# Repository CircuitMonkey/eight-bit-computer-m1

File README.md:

# eight-bit-computer-m1
Surface Mount Technology (SMT) implementation of Ben Eater's 8-bit Computer

The "M1" project is a Surface Mount Technology (SMT) implementation of [Ben Eater's 8-bit computer project](https://eater.net/8bit) as a compact and modular kit designed in Autodesk Eagle.   If you don't want to mess with SMT or Eagle, Ben has made his kit PCB available in KiCAD already,  or consider purchasing his kit.

For this implementation, I have re-entered all of the design files and created new suirface-mount library components into Eagle, by hand.  Therefore there are likely to be a few errors or unexpected differences encountered. Your feedback would be much appreciated.

Circuit Monkey is not affiliated with Ben Eater. However, if you appreciate this or Ben's project, please consider supporting Ben's work directly and financially using any one of the methods listed on his website.

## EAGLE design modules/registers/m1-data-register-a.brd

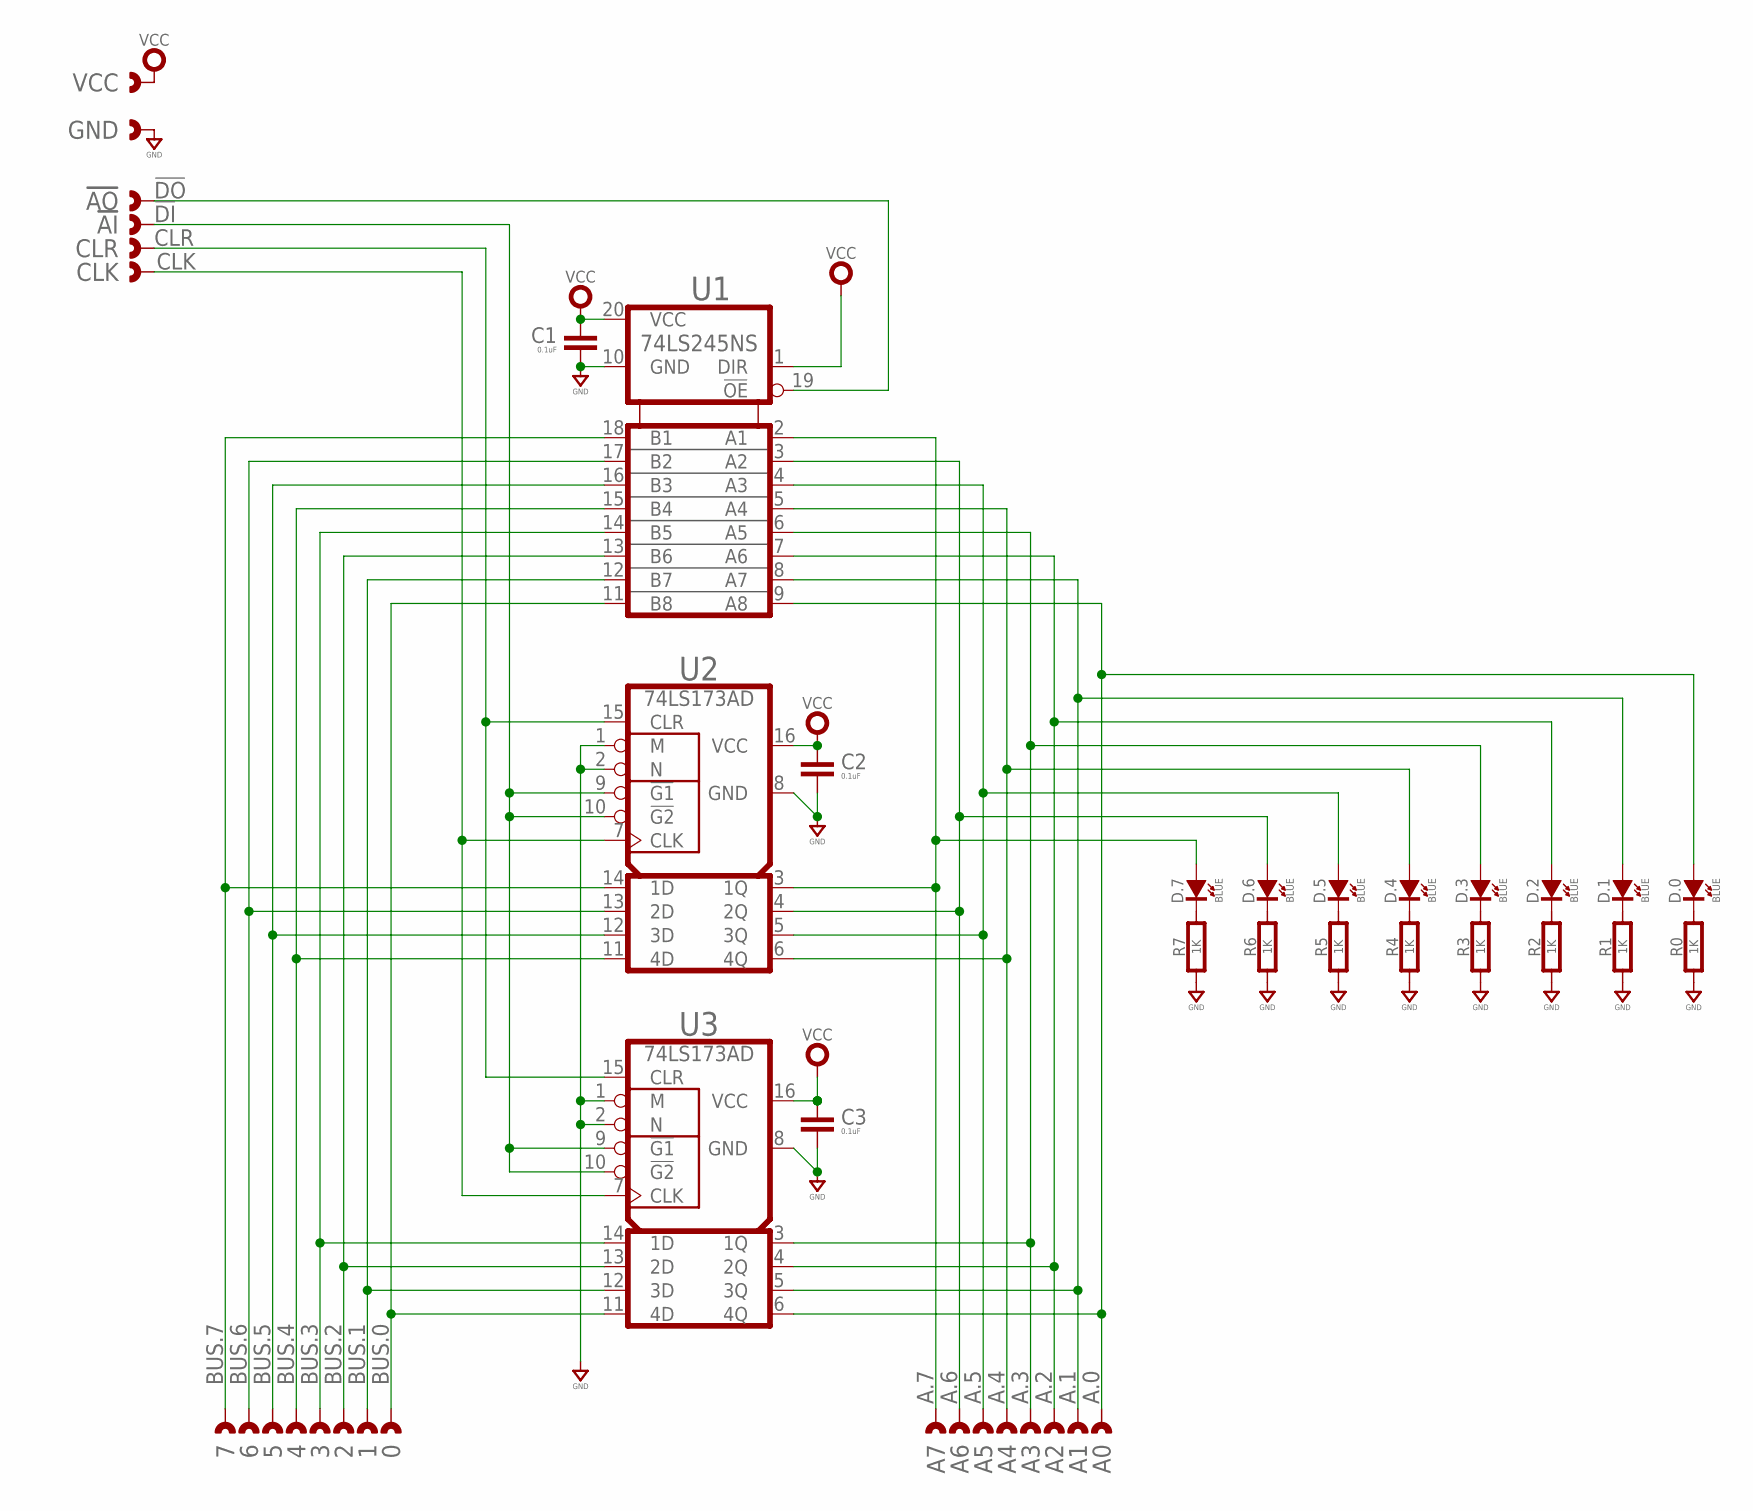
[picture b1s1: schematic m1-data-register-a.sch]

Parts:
0, 1, 2, 3, 4, 5, 6, 7: CAST-01X1; CAST01-2.54MM
!AI: CAST-01X1; CAST01-2.54MM
!AO: CAST-01X1; CAST01-2.54MM
A0, A1, A2, A3, A4, A5, A6, A7: CAST-01X1; CAST01-2.54MM
C1, C2, C3: 0.1uF; 0603-CAP
CLK: CAST-01X1; CAST01-2.54MM
CLR: CAST-01X1; CAST01-2.54MM
D.0, D.1, D.2, D.3, D.4, D.5, D.6, D.7: BLUE; SMD_0603
GND: CAST-01X1; CAST01-2.54MM
R0, R1, R2, R3, R4, R5, R6, R7: 1K; 0603-RES
U1: 74LS245NS; SO20
U2, U3: 74LS173AD; SO16
VCC: CAST-01X1; CAST01-2.54MM

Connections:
!DI: !AI.1, U2.9 (!G1), U2.10 (!G2), U3.9 (!G1), U3.10 (!G2)
!DO: !AO.1, U1.19 (!OE)
A.0: A0.1, D.0.A, U1.9 (A8), U3.6 (4Q)
A.1: A1.1, D.1.A, U1.8 (A7), U3.5 (3Q)
A.2: A2.1, D.2.A, U1.7 (A6), U3.4 (2Q)
A.3: A3.1, D.3.A, U1.6 (A5), U3.3 (1Q)
A.4: A4.1, D.4.A, U1.5 (A4), U2.6 (4Q)
A.5: A5.1, D.5.A, U1.4 (A3), U2.5 (3Q)
A.6: A6.1, D.6.A, U1.3 (A2), U2.4 (2Q)
A.7: A7.1, D.7.A, U1.2 (A1), U2.3 (1Q)
BUS.0: 0.1, U1.11 (B8), U3.11 (4D)
BUS.1: 1.1, U1.12 (B7), U3.12 (3D)
BUS.2: 2.1, U1.13 (B6), U3.13 (2D)
BUS.3: 3.1, U1.14 (B5), U3.14 (1D)
BUS.4: 4.1, U1.15 (B4), U2.11 (4D)
BUS.5: 5.1, U1.16 (B3), U2.12 (3D)
BUS.6: 6.1, U1.17 (B2), U2.13 (2D)
BUS.7: 7.1, U1.18 (B1), U2.14 (1D)
CLK: CLK.1, U2.7 (CLK), U3.7 (CLK)
CLR: CLR.1, U2.15 (CLR), U3.15 (CLR)
GND: C1.2, C2.2, C3.2, GND.1, R0.1, R1.1, R2.1, R3.1, R4.1, R5.1, R6.1, R7.1, U1.10 (GND), U2.1 (M), U2.2 (N), U2.8 (GND), U3.1 (M), U3.2 (N), U3.8 (GND)
unnamed: D.0.K (C), R0.2
unnamed: D.1.K (C), R1.2
unnamed: D.2.K (C), R2.2
unnamed: D.3.K (C), R3.2
unnamed: D.4.K (C), R4.2
unnamed: D.5.K (C), R5.2
unnamed: D.6.K (C), R6.2
unnamed: D.7.K (C), R7.2
VCC: C1.1, C2.1, C3.1, U1.1 (DIR), U1.20 (VCC), U2.16 (VCC), U3.16 (VCC), VCC.1

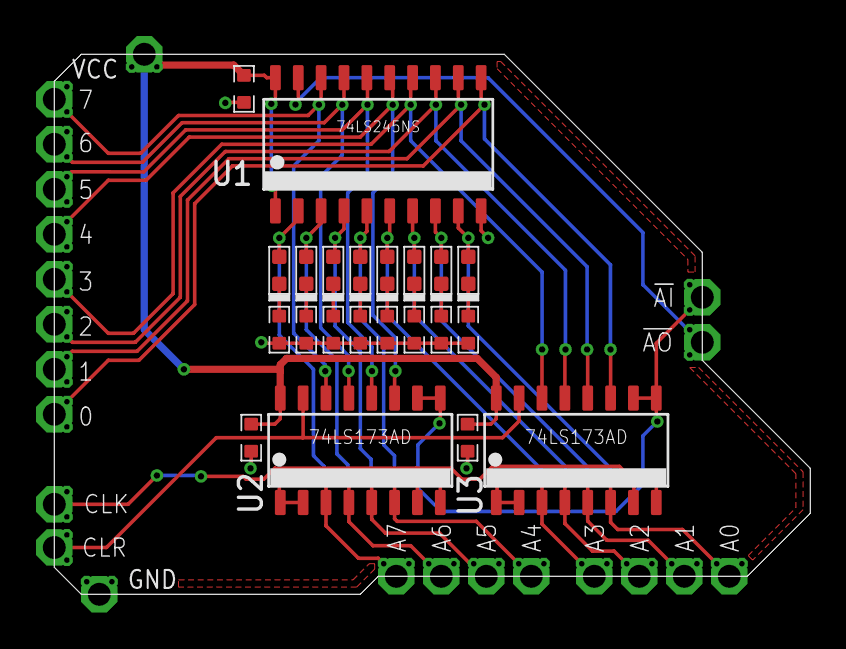
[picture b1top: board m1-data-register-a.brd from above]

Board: 2 copper layers, 42.0 x 30.0 mm, 44 parts (0 on the bottom side), 30 nets.

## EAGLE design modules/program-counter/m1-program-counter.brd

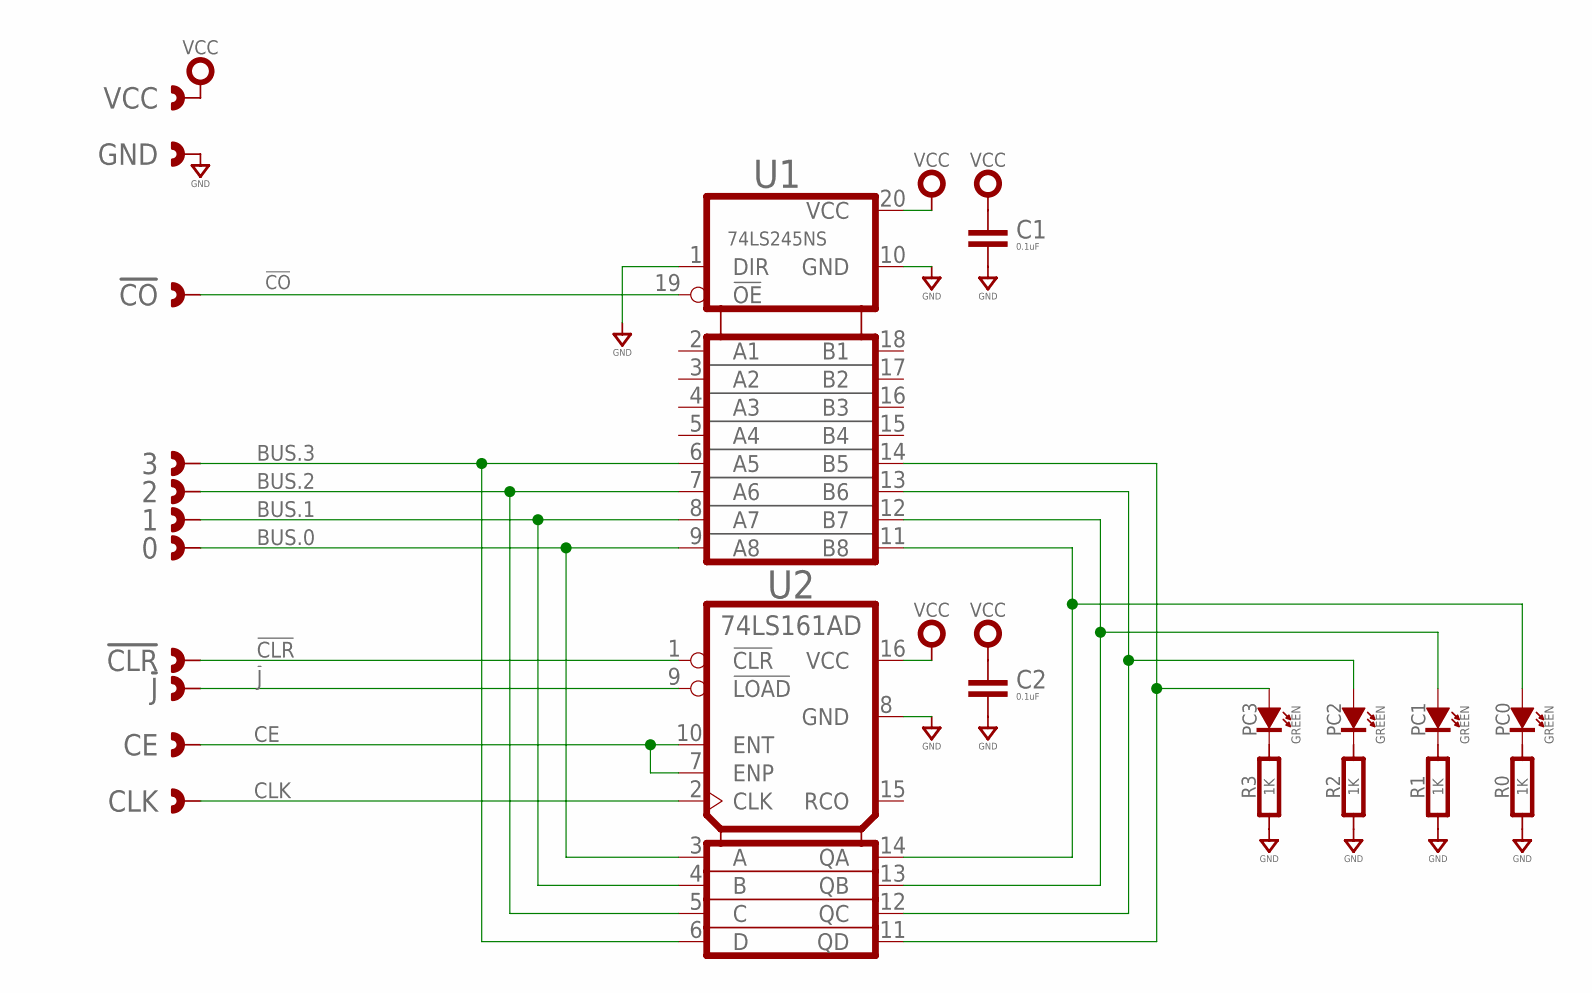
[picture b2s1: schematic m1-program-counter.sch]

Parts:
0, 1, 2, 3: CAST-01X1; CAST01-2.54MM
!CLR: CAST-01X1; CAST01-2.54MM
!CO: CAST-01X1; CAST01-2.54MM
!J: CAST-01X1; CAST01-2.54MM
C1, C2: 0.1uF; 0603-CAP
CE: CAST-01X1; CAST01-2.54MM
CLK: CAST-01X1; CAST01-2.54MM
GND: CAST-01X1; CAST01-2.54MM
PC0, PC1, PC2, PC3: GREEN; SMD_0603
R0, R1, R2, R3: 1K; 0603-RES
U1: 74LS245NS; SO20
U2: 74LS161AD; SO16
VCC: CAST-01X1; CAST01-2.54MM

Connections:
!CLR: !CLR.1, U2.1 (!CLR)
!CO: !CO.1, U1.19 (!OE)
!J: !J.1, U2.9 (!LOAD)
BUS.0: 0.1, U1.9 (A8), U2.3 (A)
BUS.1: 1.1, U1.8 (A7), U2.4 (B)
BUS.2: 2.1, U1.7 (A6), U2.5 (C)
BUS.3: 3.1, U1.6 (A5), U2.6 (D)
CE: CE.1, U2.7 (ENP), U2.10 (ENT)
CLK: CLK.1, U2.2 (CLK)
GND: C1.2, C2.2, GND.1, R0.1, R1.1, R2.1, R3.1, U1.1 (DIR), U1.10 (GND), U2.8 (GND)
unnamed: PC0.A, U1.11 (B8), U2.14 (QA)
unnamed: PC1.A, U1.12 (B7), U2.13 (QB)
unnamed: PC2.A, U1.13 (B6), U2.12 (QC)
unnamed: PC3.A, U1.14 (B5), U2.11 (QD)
unnamed: PC0.K (C), R0.2
unnamed: PC1.K (C), R1.2
unnamed: PC2.K (C), R2.2
unnamed: PC3.K (C), R3.2
VCC: C1.1, C2.1, U1.20 (VCC), U2.16 (VCC), VCC.1

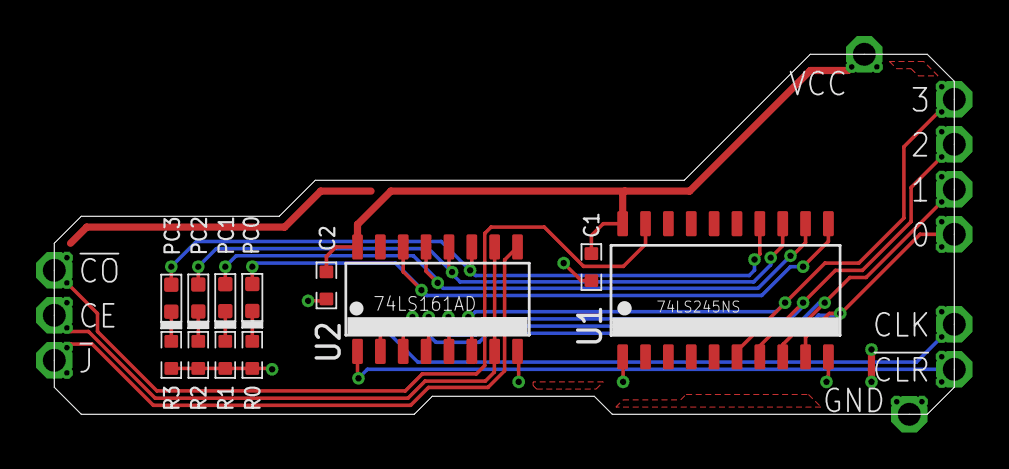
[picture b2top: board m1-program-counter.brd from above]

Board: 2 copper layers, 50.0 x 20.0 mm, 23 parts (0 on the bottom side), 19 nets.

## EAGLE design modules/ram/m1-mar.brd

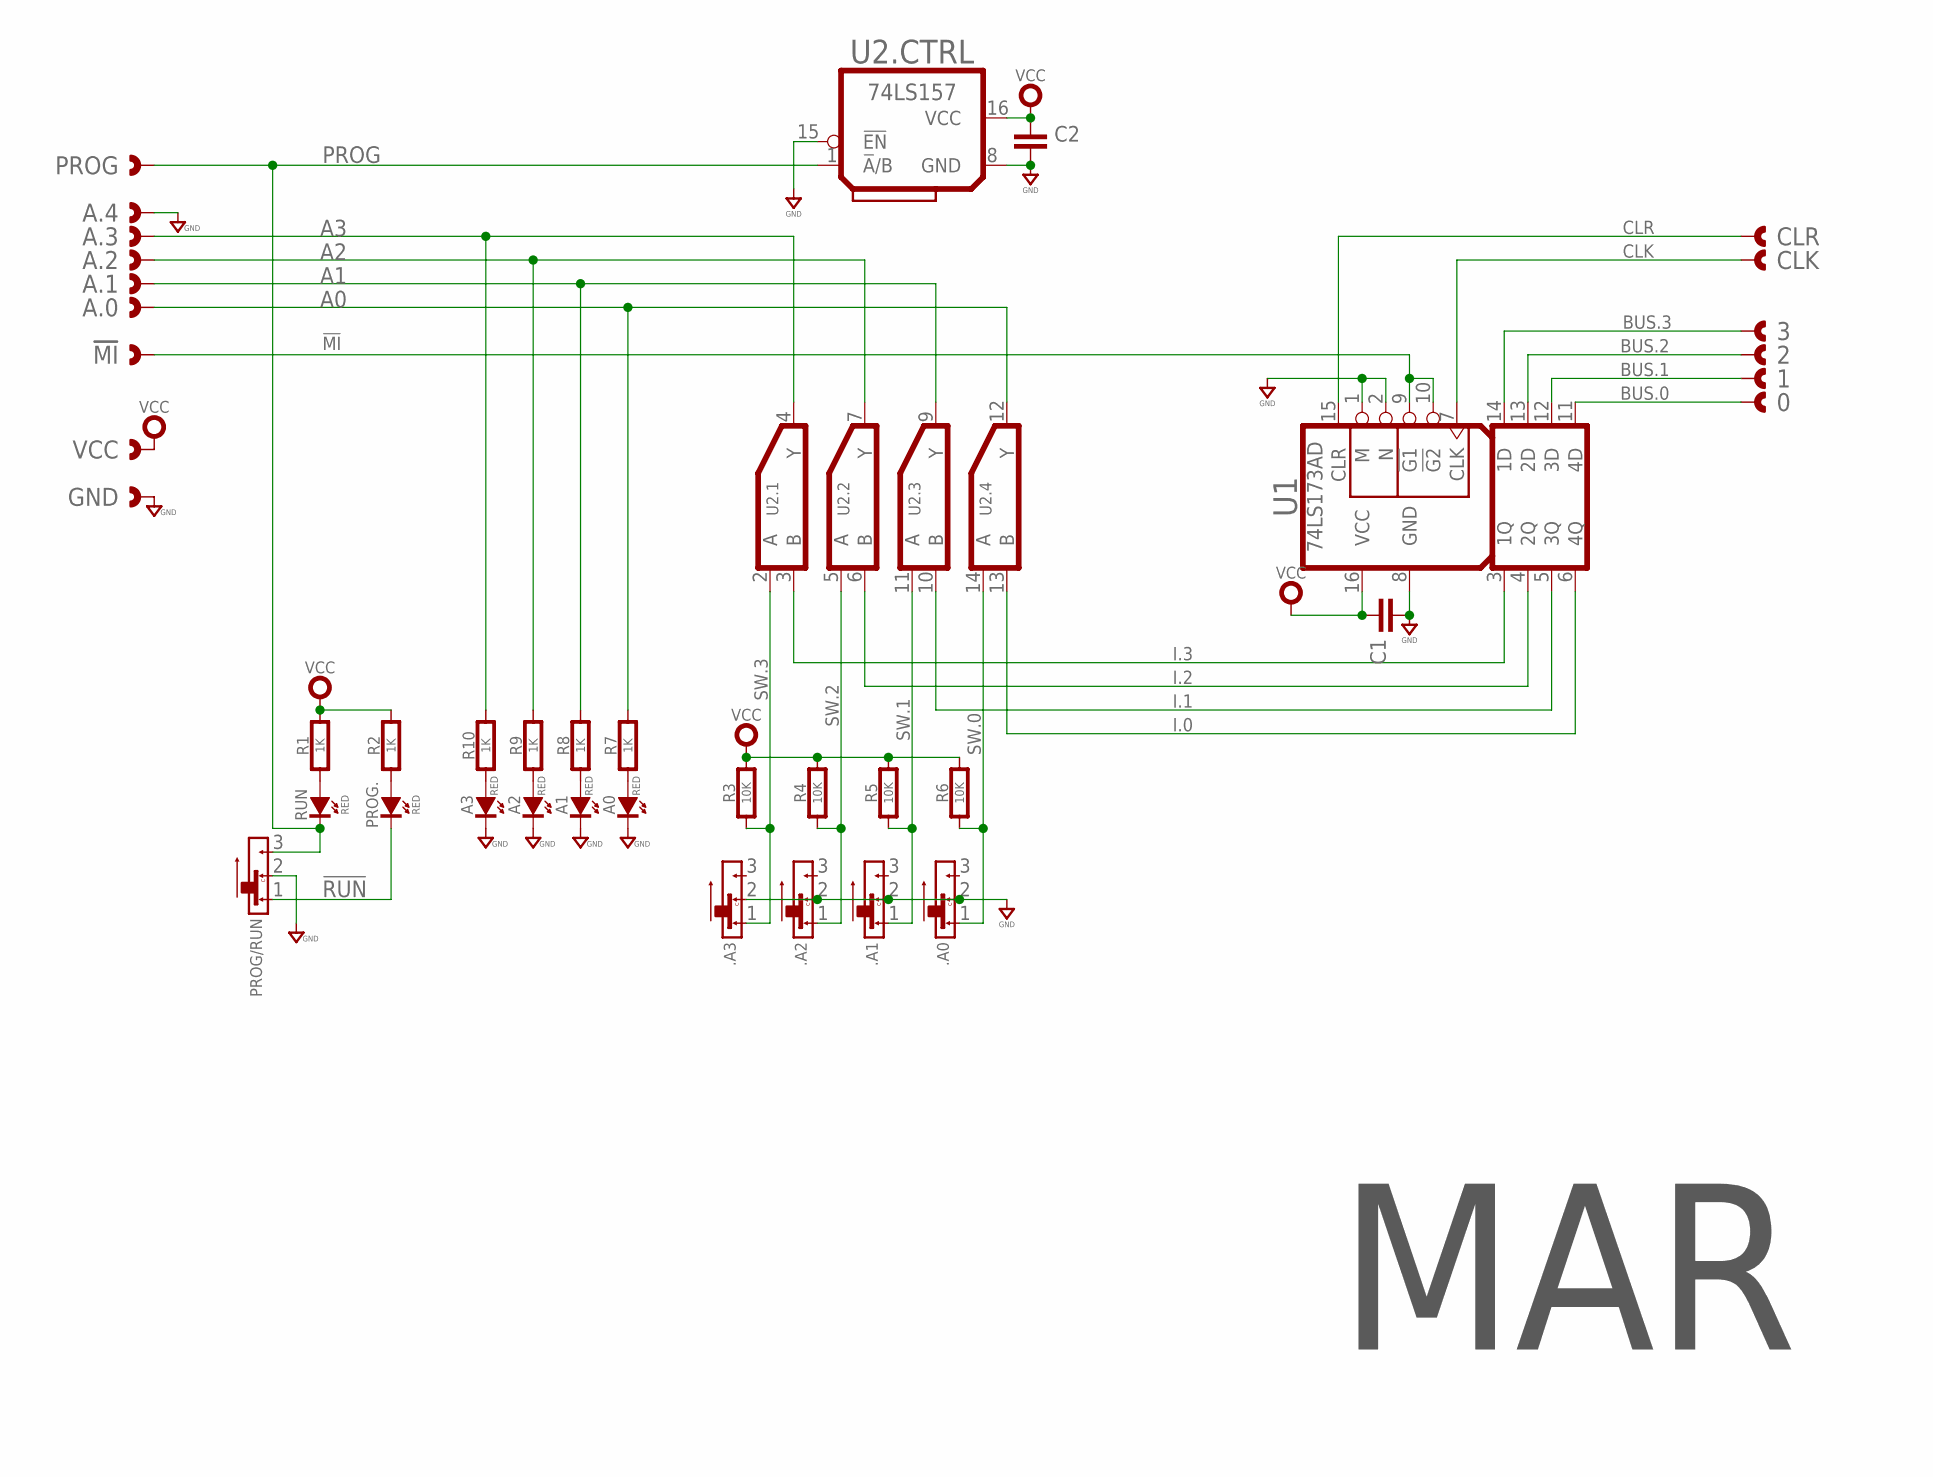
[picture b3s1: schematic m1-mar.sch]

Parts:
0, 1, 2, 3: CAST-01X1; CAST01-2.54MM
!MI: CAST-01X1; CAST01-2.54MM
.A0, .A1, .A2, .A3: SLIDE-SPDTJS102011JCQN; CK_JS102011JCQN
A0, A1, A2, A3: RED; SMD_0603
A.0, A.1, A.2, A.3, A.4: CAST-01X1; CAST01-2.54MM
C1, C2: CAPACITOR0603; 0603-CAP
CLK: CAST-01X1; CAST01-2.54MM
CLR: CAST-01X1; CAST01-2.54MM
GND: CAST-01X1; CAST01-2.54MM
PROG: CAST-01X1; CAST01-2.54MM
PROG.: RED; SMD_0603
PROG/RUN: SLIDE-SPDTJS102011JCQN; CK_JS102011JCQN
R1, R2, R7, R8, R9, R10: 1K; 0603-RES
R3, R4, R5, R6: 10K; 0603-RES
RUN: RED; SMD_0603
U1: 74LS173AD; SO16
U2: 74LS157; SO16
VCC: CAST-01X1; CAST01-2.54MM

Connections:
!MI: !MI.1, U1.9 (!G1), U1.10 (!G2)
!RUN: PROG..K (C), PROG/RUN.1
A0: A.0.1, R7.2, U2.12 (Y)
A1: A.1.1, R8.2, U2.9 (Y)
A2: A.2.1, R9.2, U2.7 (Y)
A3: A.3.1, R10.2, U2.4 (Y)
BUS.0: 0.1, U1.11 (4D)
BUS.1: 1.1, U1.12 (3D)
BUS.2: 2.1, U1.13 (2D)
BUS.3: 3.1, U1.14 (1D)
CLK: CLK.1, U1.7 (CLK)
CLR: CLR.1, U1.15 (CLR)
GND: .A0.2, .A1.2, .A2.2, .A3.2, A0.K (C), A1.K (C), A2.K (C), A3.K (C), A.4.1, C1.2, C2.2, GND.1, PROG/RUN.2, U1.1 (M), U1.2 (N), U1.8 (GND), U2.8 (GND), U2.15 (!EN)
I.0: U1.6 (4Q), U2.13 (B)
I.1: U1.5 (3Q), U2.10 (B)
I.2: U1.4 (2Q), U2.6 (B)
I.3: U1.3 (1Q), U2.3 (B)
unnamed: A0.A, R7.1
unnamed: R1.1, RUN.A
unnamed: PROG..A, R2.1
unnamed: A1.A, R8.1
unnamed: A2.A, R9.1
unnamed: A3.A, R10.1
PROG: PROG.1, PROG/RUN.3, RUN.K (C), U2.1 (!A!/B)
SW.0: .A0.1, R6.1, U2.14 (A)
SW.1: .A1.1, R5.1, U2.11 (A)
SW.2: .A2.1, R4.1, U2.5 (A)
SW.3: .A3.1, R3.1, U2.2 (A)
VCC: C1.1, C2.1, R1.2, R2.2, R3.2, R4.2, R5.2, R6.2, U1.16 (VCC), U2.16 (VCC), VCC.1

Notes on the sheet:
MAR

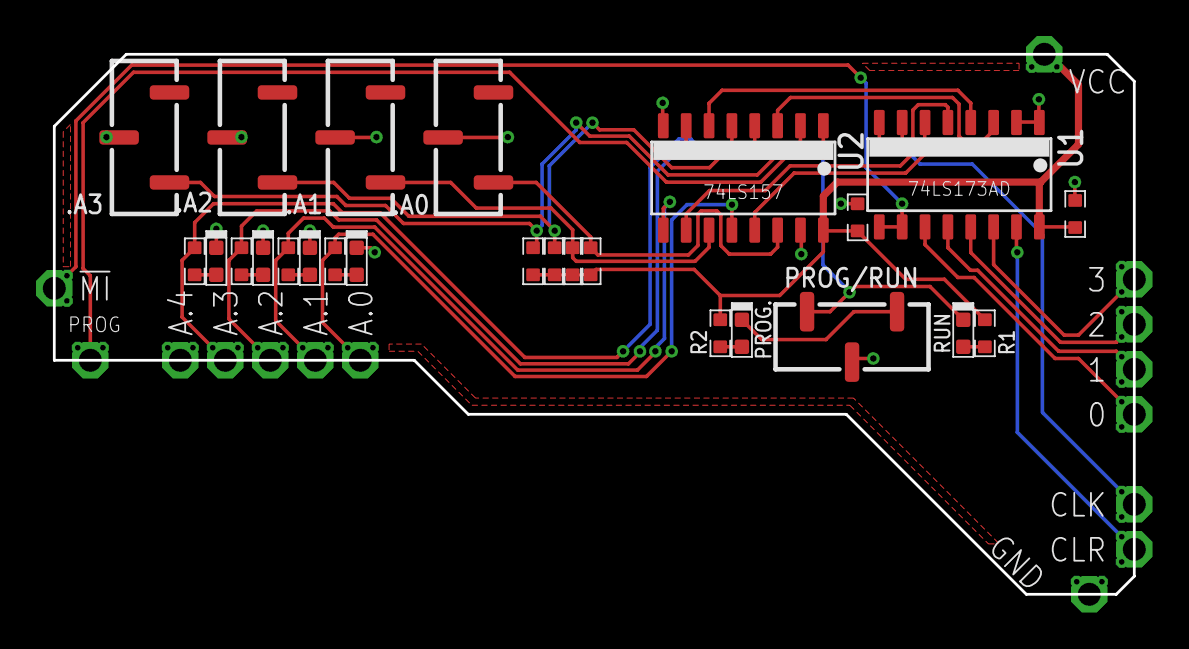
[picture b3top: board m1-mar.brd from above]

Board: 2 copper layers, 60.0 x 30.0 mm, 40 parts (0 on the bottom side), 29 nets.

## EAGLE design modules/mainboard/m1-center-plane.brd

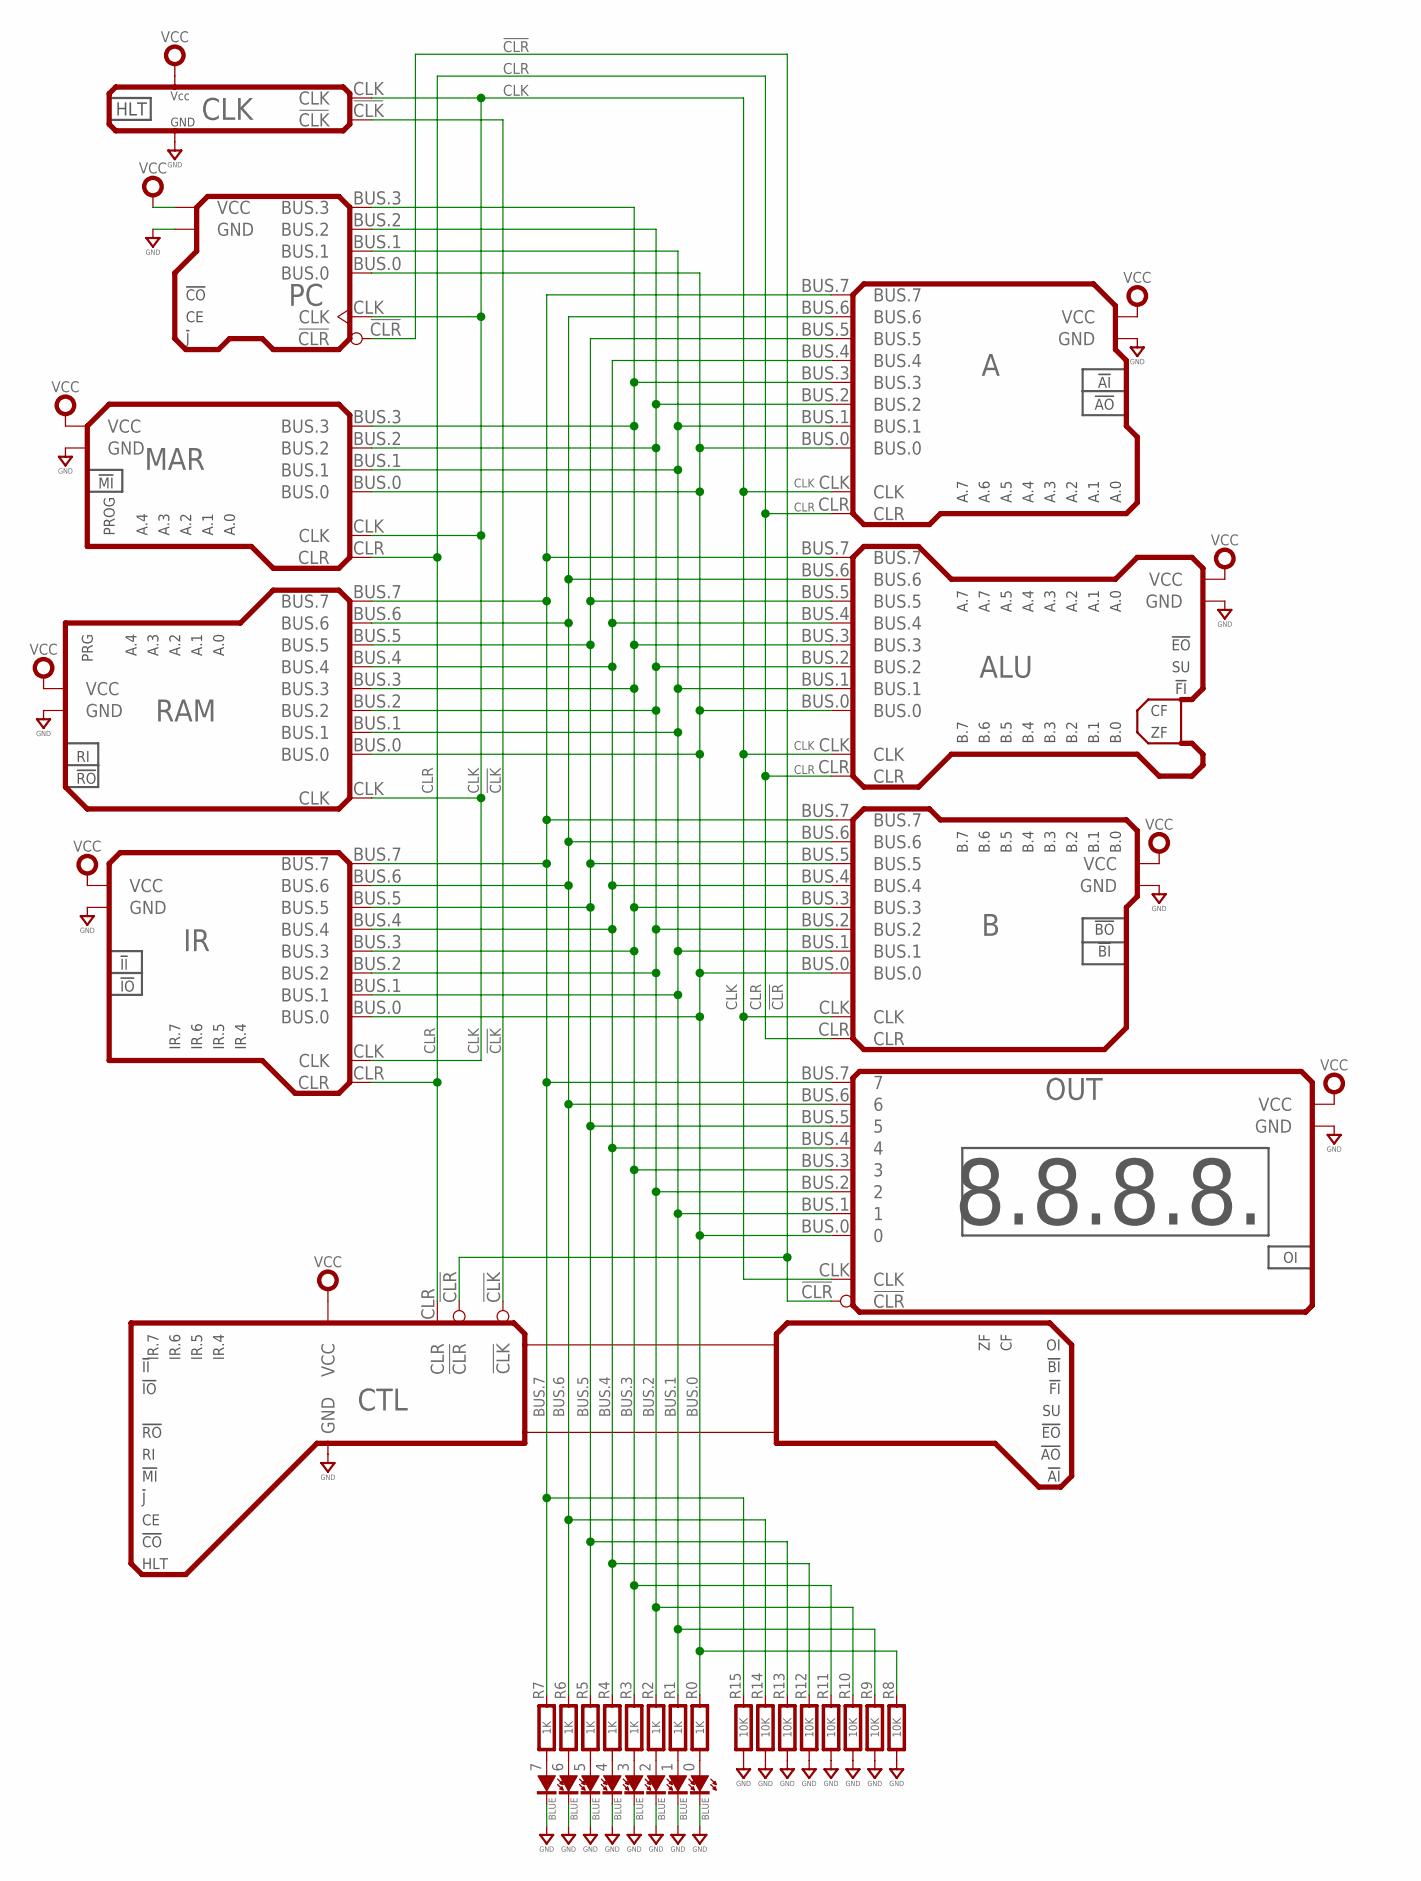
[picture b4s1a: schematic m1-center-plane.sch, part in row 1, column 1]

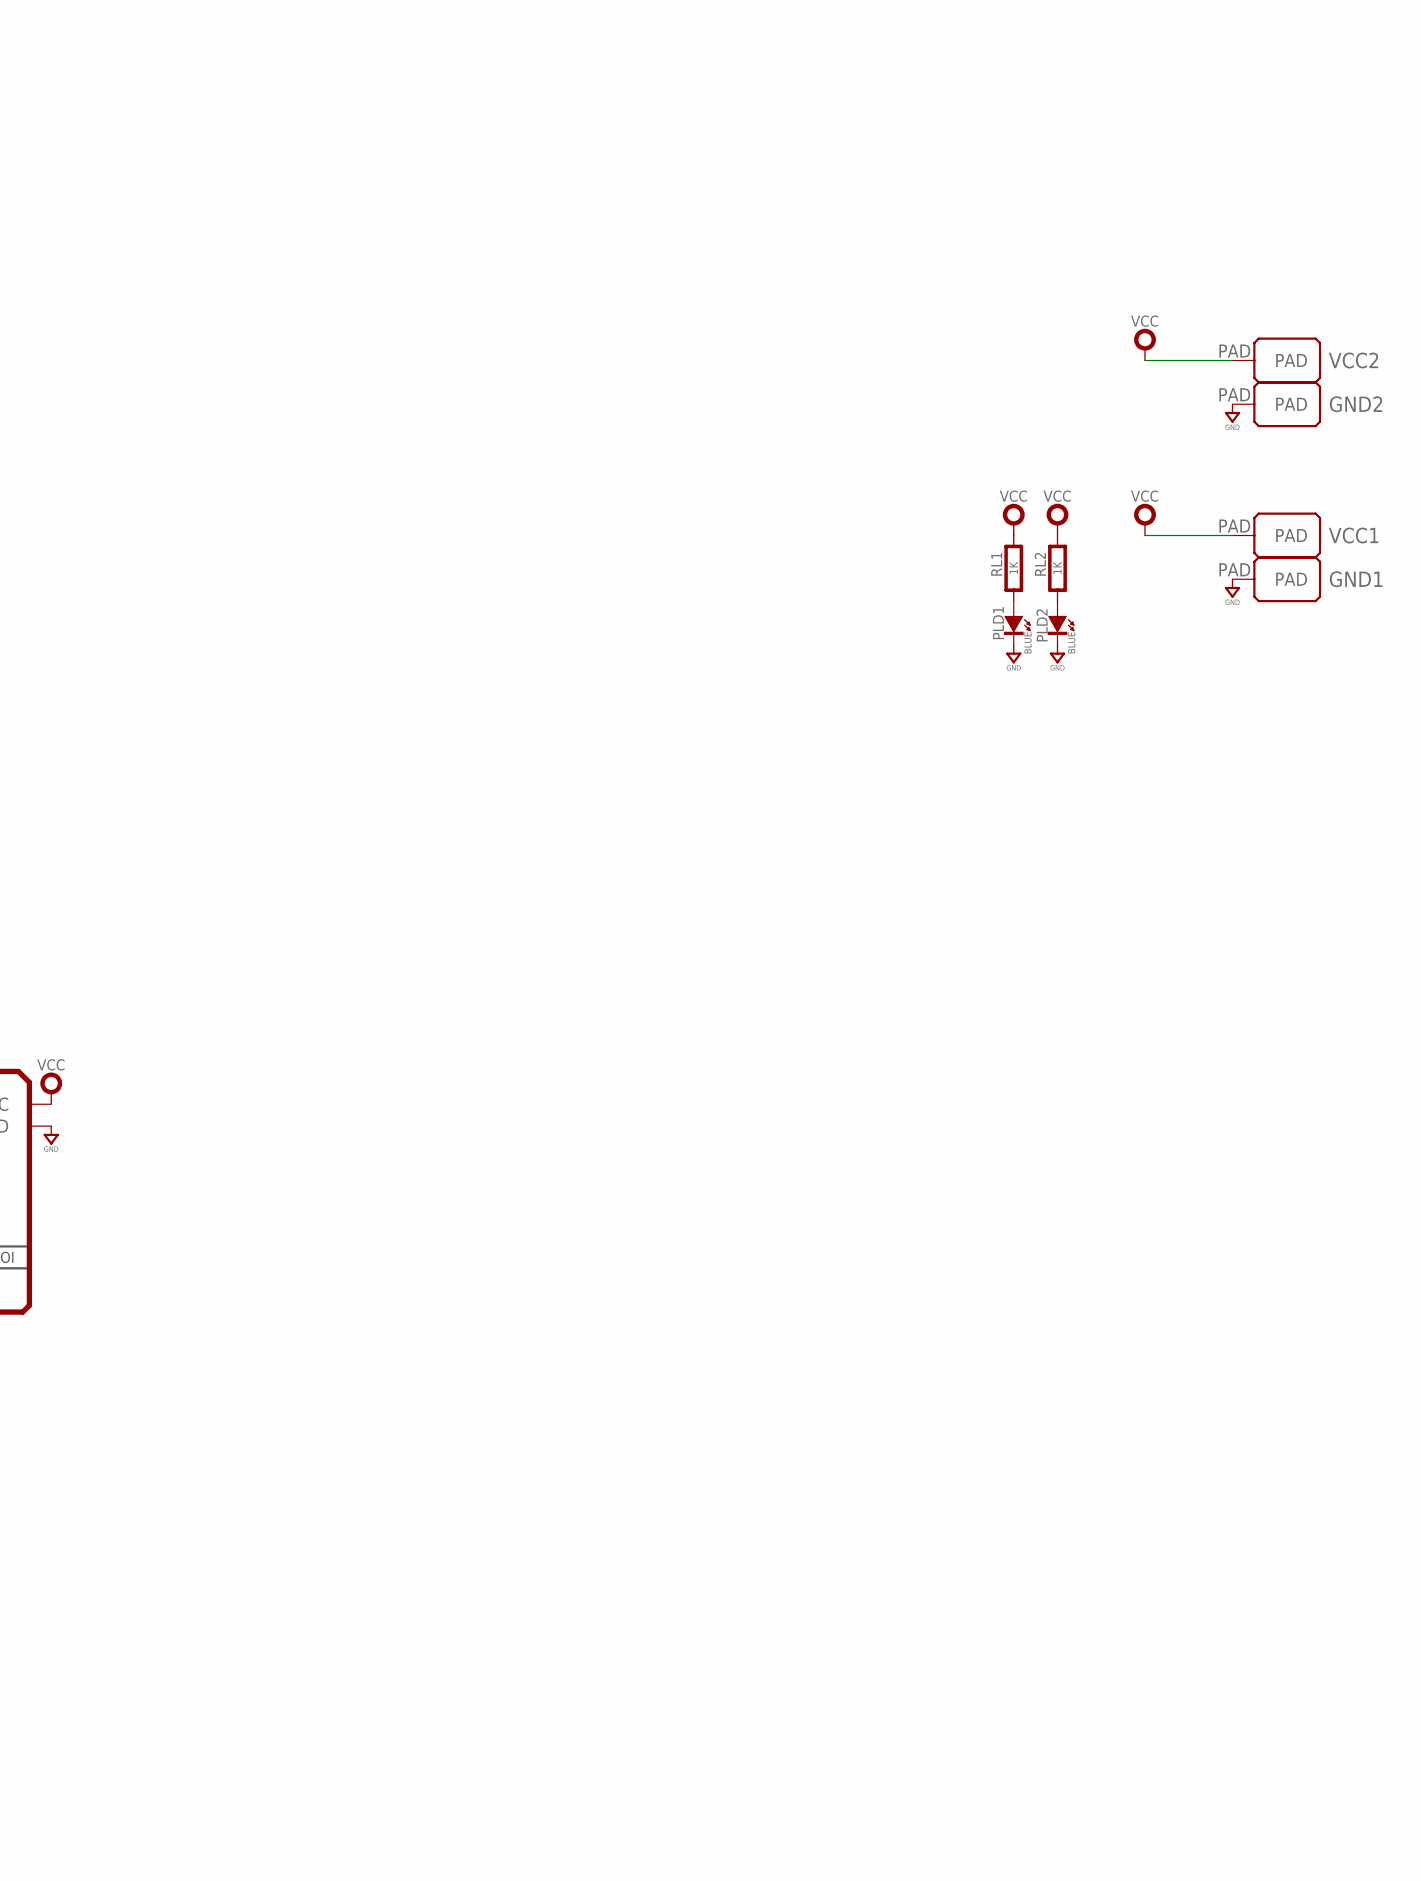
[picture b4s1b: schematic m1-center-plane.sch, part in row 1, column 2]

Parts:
0, 1, 2, 3, 4, 5, 6, 7: BLUE; SMD_0603
A: M1-REG-A-BUS
ALU: M1-ALU-BUS
B: M1-REG-B-BUS
CLK: M1-CLOCK-BUS
CTL: M1-CONTROL-BUS
GND1, GND2: PADSMD-100X100; SMD-100X100
IR: M1-REG-INSTR-BUS; M1-REG-I-BUS
MAR: M1-MAR-BUS
OUT: M1-REG-OUTPUT-BUS
PC: M1-PROG-COUNTER-BUS; M1-PROGRAM-COUNTER-BUS
PLD1, PLD2: BLUE; SMD_0603
R0, R1, R2, R3, R4, R5, R6, R7: 1K; 0603-RES
R8, R9, R10, R11, R12, R13, R14, R15: 10K; 0603-RES
RAM: M1-RAM-BUS
RL1, RL2: 1K; 0603-RES
VCC1, VCC2: PADSMD-100X100; SMD-100X100

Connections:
!CLK: CLK.!CLK, CTL.!CLK
!CLR: CTL.!CLR, OUT.!CLR, PC.!CLR
BUS.0: A.BUS.0, ALU.BUS.0, B.BUS.0, IR.BUS.0, MAR.BUS.0, OUT.BUS.0 (0), PC.BUS.0, R0.2, R8.2, RAM.BUS.0
BUS.1: A.BUS.1, ALU.BUS.1, B.BUS.1, IR.BUS.1, MAR.BUS.1, OUT.BUS.1 (1), PC.BUS.1, R1.2, R9.2, RAM.BUS.1
BUS.2: A.BUS.2, ALU.BUS.2, B.BUS.2, IR.BUS.2, MAR.BUS.2, OUT.BUS.2 (2), PC.BUS.2, R2.2, R10.2, RAM.BUS.2
BUS.3: A.BUS.3, ALU.BUS.3, B.BUS.3, IR.BUS.3, MAR.BUS.3, OUT.BUS.3 (3), PC.BUS.3, R3.2, R11.2, RAM.BUS.3
BUS.4: A.BUS.4, ALU.BUS.4, B.BUS.4, IR.BUS.4, OUT.BUS.4 (4), R4.2, R12.2, RAM.BUS.4
BUS.5: A.BUS.5, ALU.BUS.5, B.BUS.5, IR.BUS.5, OUT.BUS.5 (5), R5.2, R13.2, RAM.BUS.5
BUS.6: A.BUS.6, ALU.BUS.6, B.BUS.6, IR.BUS.6, OUT.BUS.6 (6), R6.2, R14.2, RAM.BUS.6
BUS.7: A.BUS.7, ALU.BUS.7, B.BUS.7, IR.BUS.7, OUT.BUS.7 (7), R7.2, R15.2, RAM.BUS.7
CLK: A.CLK, ALU.CLK, B.CLK, CLK.CLK, IR.CLK, MAR.CLK, OUT.CLK, PC.CLK, RAM.CLK
CLR: A.CLR, ALU.CLR, B.CLR, CTL.CLR, IR.CLR, MAR.CLR
GND: 0.K (C), 1.K (C), 2.K (C), 3.K (C), 4.K (C), 5.K (C), 6.K (C), 7.K (C), A.GND, ALU.GND, B.GND, CLK.GND, CTL.GND, GND1.PAD, GND2.PAD, IR.GND, MAR.GND, OUT.GND, PC.GND, PLD1.K (C), PLD2.K (C), R8.1, R9.1, R10.1, R11.1, R12.1, R13.1, R14.1, R15.1, RAM.GND
unnamed: 0.A, R0.1
unnamed: 1.A, R1.1
unnamed: 2.A, R2.1
unnamed: 3.A, R3.1
unnamed: 4.A, R4.1
unnamed: 5.A, R5.1
unnamed: 6.A, R6.1
unnamed: 7.A, R7.1
unnamed: PLD2.A, RL2.1
unnamed: PLD1.A, RL1.1
VCC: A.VCC, ALU.VCC, B.VCC, CLK.VCC, CTL.VCC, IR.VCC, MAR.VCC, OUT.VCC, PC.VCC, RAM.VCC, RL1.2, RL2.2, VCC1.PAD, VCC2.PAD

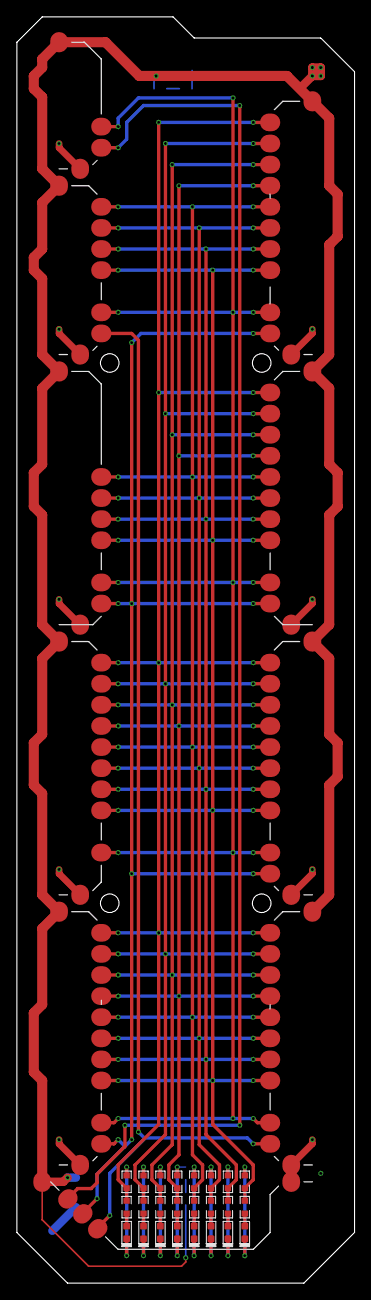
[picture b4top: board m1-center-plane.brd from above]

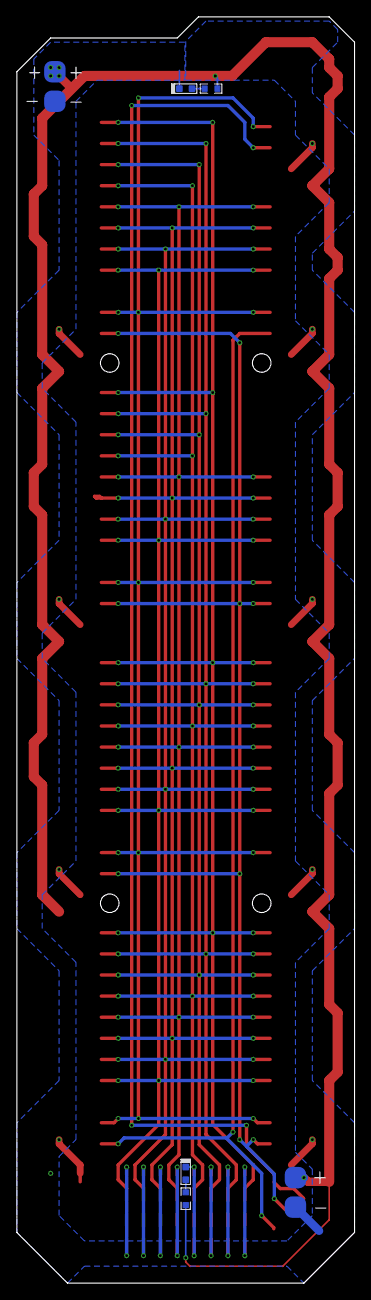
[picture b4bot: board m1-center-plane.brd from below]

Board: 2 copper layers, 40.0 x 150.0 mm, 42 parts (8 on the bottom side), 24 nets.
